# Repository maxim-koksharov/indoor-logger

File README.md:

# Air Quality Monitor — ESP8266 RTOS SDK

ESP8266-based indoor air quality monitoring system with OLED display, ENS160+AHT21 sensors, WiFi data sync, and a web dashboard.

## System Overview

Two ESP8266 devices communicating over WiFi (both connect to your home router):

```
┌────────────────────┐      WiFi (STA)       ┌────────────────────┐
│   Server (16MB)    │◄─────────────────────►│   Client (4MB)     │
│                    │    Your Home Router   │                    │
│  STA mode          │      192.168.x.x      │  STA mode          │
│  HTTP REST API     │                       │  OLED Display      │
│  Web Dashboard     │                       │  ENS160 + AHT21    │
│  Data Aggregation  │                       │  Local SPIFFS      │
│  UDP discovery     │                       │  WiFi sync         │
│  Backup WiFi       │                       │  UDP discovery     │
│  Timezone config   │                       │  Fallback SERVER_IP│
└────────────────────┘                       └────────────────────┘
```

**WiFi Mode:**
- **Server**: STA-only (connects to your router). Supports primary + backup SSID.
- **Client**: STA-only (connects to the same router). Discovers server via UDP broadcast.

**Server Discovery:** Client sends UDP broadcast to port 5000. Server responds with its IP. No static IP needed.

## Hardware Requirements

- 2× Wemos D1 Mini (ESP8266EX) — 4MB flash for the client, 16MB for the server
- 1× ENS160 + AHT21 air quality sensor module (I2C)
- 1× 0.91" SSD1306 OLED display 128×32 (I2C)
- 1× Tactile button (optional, GPIO12)
- Breadboard and jumper wires

### Wiring

All three I2C devices share a single bus (bus 0):

| Wemos Pin | GPIO | Connection |
|---|---|---|
| D1 | GPIO5 | I2C SCL (OLED + ENS160 + AHT21) |
| D2 | GPIO4 | I2C SDA (OLED + ENS160 + AHT21) |
| D5 | GPIO14 | Output LOW (button GND) |
| D6 | GPIO12 | Input pull-up (button sense) |
| 3V3 | — | VCC (all modules) |
| GND | — | GND (all modules) |

| Device | I2C Address |
|---|---|
| SSD1306 OLED | `0x3C` |
| ENS160 | `0x53` |
| AHT21 | `0x38` |

## Build System

The project uses the standard ESP-IDF CMake build system.
**SDK**: ESP8266 RTOS SDK v3.4 (`/esp/ESP8266_RTOS_SDK`)
**Toolchain**: `/esp/bin/xtensa-lx106-elf/bin`

All commands run inside the Docker container (see `AGENTS.md` for build/run instructions).

### Menuconfig (one-time setup)

```bash
# Client: Client ID, WiFi SSID/pass
idf.py -C apps/client menuconfig

# Server: WiFi SSID/pass (primary + backup)
idf.py -C apps/server menuconfig
```

### Build

```bash
idf.py -C apps/client build
idf.py -C apps/server build
```

### Flash

```bash
idf.py -C apps/client -p /dev/ttyUSB0 flash
idf.py -C apps/server -p /dev/ttyUSB1 flash
```

### Clean

```bash
idf.py -C apps/client fullclean
idf.py -C apps/server fullclean
```

> For the full command list, including monitor and erase, see `AGENTS.md`.

## WiFi Configuration

WiFi SSID and password are read from `/workspace/wifi.env` at build time. Create the file (it is gitignored):

```bash
cat > /workspace/wifi.env <<EOF
WIFI_SSID=MyHomeWiFi
WIFI_PASS=MyPassword
SERVER_IP=192.168.1.100
EOF
```

`SERVER_IP` is optional. It is used by the client as a fallback when UDP broadcast discovery is blocked by the router.

You can still override credentials via `menuconfig` or NVS if needed.

### Server

```bash
idf.py -C apps/server menuconfig
# Server Configuration → Primary WiFi SSID & Password
#                      → Backup WiFi SSID & Password (optional)
idf.py -C apps/server build
idf.py -C apps/server -p /dev/ttyUSB1 flash
```

**Operating mode:**
- The server connects to your router (STA mode)
- Supports a primary and a backup WiFi network (switches after 3 failed attempts)
- Runs a UDP discovery service on port 5000
- The client finds the server automatically via UDP broadcast
- When the network is unreachable → retries connection every 60 sec
- On wrong password → retries every 60 min

**NVS (alternative to menuconfig):**
Credentials can be stored in NVS (survives reflash):
```c
// Via provisioning or a debug script:
nvs_set_str("wifi", "sta_ssid", "YourNetwork");
nvs_set_str("wifi", "sta_pass", "YourPassword");
nvs_commit();
```
NVS takes precedence over menuconfig.

### Client

```bash
idf.py -C apps/client menuconfig
# Client Configuration → Client device identifier
#                      → WiFi SSID (same as server)
#                      → WiFi password (same as server)
idf.py -C apps/client build
idf.py -C apps/client -p /dev/ttyUSB0 flash
```

**Operating mode:**
- The client connects to the same router (STA mode)
- Sends a UDP broadcast on port 5000 to discover the server
- Automatically uses the IP returned by the server for data uploads
- Falls back to `SERVER_IP` from `wifi.env` if broadcast discovery is blocked
- Runs a state machine:
  - `DISCOVERING` — connect to WiFi, discover server
  - `CONNECTED` — upload records, apply server config, sleep for sync interval
  - `AUTONOMOUS` — keep reading sensors locally, retry discovery every hour

### What is `menuconfig` and why do I need it?

`idf.py menuconfig` opens a text-based project configuration UI.
It lets you change build parameters without editing source files:

**WiFi credentials** are read from `wifi.env` at build time. Use `menuconfig` only if you want to override them or store them in the firmware image directly.

**For the client** (`Client Configuration`):
- `Client device identifier` — unique device ID (default `test_client`).
  Used as `?id=<client_id>` when uploading to the server.
- `Display timeout` — auto-off timeout in seconds (0 = always on).
- `Discovery timeout / retry interval / default sync interval` — discovery and sync behavior.

Changes are saved in `sdkconfig` and applied on `idf.py build`.
The config options are exposed in code as `CONFIG_CLIENT_ID`, etc.

**Display:** Off by default. Turns on for 6 seconds on a button press
(2 screens × 3 seconds: temp/time → CO₂/VOC/AQI).

### Serial Monitor

`idf.py monitor` does not work inside Docker (termios error).
Use this Python script instead:

```bash
python3 -c "
import serial, time
ser = serial.Serial('/dev/ttyUSB0', 74880, timeout=1)
ser.dtr = False; ser.rts = True; time.sleep(0.1); ser.rts = False; time.sleep(2)
buf = b''; deadline = time.time() + 10
while time.time() < deadline:
    data = ser.read(4096)
    if data: buf += data
    elif len(buf) > 0: break
ser.close(); print(buf.decode('utf-8', errors='replace'))
"
```

## USB Connection & Serial Debug

Both ESP8266 boards are connected to the host via USB and are passed through to the
container by `docker compose.yml`. All build, flash, and serial debug commands
work **from inside the container** — there is no need to switch to the host shell.

### Device Mapping

| Host device | Board | Used for |
|---|---|---|
| `/dev/ttyUSB0` | Client (Wemos D1 Mini + OLED + ENS160 + AHT21) | Flash, monitor, debug |
| `/dev/ttyUSB1` | Server (Wemos D1 Mini, 16MB flash) | Flash, monitor, debug |

The container is configured with:
- `devices:` passing `/dev/ttyUSB0` and `/dev/ttyUSB1` through
- `device_cgroup_rules: c 188:* rmw` to allow `esptool` / `idf.py` to manage them
- `group_add: ["20"]` (the `dialout` group on the host) so the in-container `dev` user
  can read/write serial ports without `sudo`

### Verifying the connection

Open a shell in the container and check that the devices are visible:

```bash
docker compose run --rm bash

# Inside the container:
ls -l /dev/ttyUSB*
# crw-rw---- 1 root dialout 188, 0 ... /dev/ttyUSB0
# crw-rw---- 1 root dialout 188, 1 ... /dev/ttyUSB1

lsusb
# Bus 001 Device 005: ID 1a86:7523 QinHeng Electronics CH340 serial converter
# ...

# Confirm the in-container user is in dialout:
id
# uid=1000(dev) gid=1000(dev) groups=1000(dev),20(dialout)
```

If `/dev/ttyUSB*` are missing, the host likely does not have permission or the
devices are not enumerated yet:

```bash
# On the host:
ls -l /dev/ttyUSB*              # check device presence
sudo usermod -aG dialout $USER  # add your user to dialout (one-time)
# then log out / log in
```

### Tailing serial output (one-shot, 10s)

Capture the boot log without leaving the container:

```bash
docker compose run --rm bash -c '
  python3 -c "
import serial, time
ser = serial.Serial(\"/dev/ttyUSB0\", 74880, timeout=1)
ser.dtr = False; ser.rts = True; time.sleep(0.1); ser.rts = False; time.sleep(2)
buf = b\"\"; deadline = time.time() + 10
while time.time() < deadline:
    data = ser.read(4096)
    if data: buf += data
    elif len(buf) > 0: break
ser.close(); print(buf.decode(\"utf-8\", errors=\"replace\"))
"
'
```

For the server, replace `/dev/ttyUSB0` with `/dev/ttyUSB1`.

### Continuous log tail (interactive)

For long-running debug sessions, keep the port open and follow output:

```bash
docker compose run --rm bash

# Inside the container:
stty -F /dev/ttyUSB0 74880 raw -echo
cat /dev/ttyUSB0
# press RST on the board to see fresh boot logs
# Ctrl-C to exit
```

### Flashing a board

Flash commands work the same as on the host — just run them from inside the container:

```bash
docker compose run --rm bash

# Inside the container:
cd /workspace/apps/client
idf.py -p /dev/ttyUSB0 flash

cd /workspace/apps/server
idf.py -p /dev/ttyUSB1 flash
```

### Troubleshooting

| Symptom | Likely cause | Fix |
|---|---|---|
| `Could not open /dev/ttyUSB0` | Device busy or not present | Unplug/replug the USB cable; check `lsusb` on the host |
| `Permission denied` on `/dev/ttyUSB*` | User not in `dialout` | `sudo usermod -aG dialout $USER` on the host, then re-login |
| `esptool: failed to connect` | Wrong port or board not in flash mode | Hold `FLASH` button on Wemos D1 Mini during reset, or check wiring |
| Container cannot see `/dev/ttyUSB*` | Device path differs (e.g. `/dev/ttyACM0`) | Edit `compose.yml` `devices:` list and `device_cgroup_rules` (use `c 166:* rmw` for ACM) |
| Garbled serial output | Wrong baud rate | Wemos D1 Mini bootloader prints at **74880 baud**, runtime at **115200** |

## Self-Test

On startup, both applications log a self-test summary.
This is the primary way to verify that everything works:

**Client:**
```
=== SELF-TEST ===
  NVS: OK
  I2C: init OK (SDA=GPIO4 SCL=GPIO5)
  Display: initialized
  ENS160: detected
  AHT21: detected
  SPIFFS: OK (total=... used=...)
  Storage: 125 records saved
  Client ID: living_room
  Heap at init: 64 KB
=== END SELF-TEST ===
```

**Server:**
```
=== SELF-TEST ===
  SPIFFS: OK (total=... used=...)
  NVS: OK
  Registry: 0 clients loaded, 16 slots free
  HTTP: OK
  SNTP: synced
  STA: connected
  STA config: YourNetwork
  Time source: NTP
  Timezone: WET0WEST,M3.5.0/1,M10.5.0/2
  IP: 192.168.1.100
  Heap: 102 KB free
=== END SELF-TEST ===
```

## API Endpoints (Server)

Once connected to the router, the server is reachable on the DHCP-assigned IP (or a static one).
Use the IP directly: `http://192.168.1.100/`

| Method | URI | Description |
|---|---|---|
| GET | `/` | Web dashboard (embedded HTML) |
| GET | `/api/health` | Server status, uptime, free heap |
| GET | `/api/clients` | List all registered clients |
| GET | `/api/client?id=<id>` | Client details + last 24 records |
| POST | `/api/upload?id=<id>` | Upload sensor data JSON. Response includes `timestamp`, `sync_interval`, `name`, `timezone` |
| GET | `/api/data?id=<id>&offset=&limit=` | Query stored records |
| GET | `/api/sync-interval` | Get current sync interval (seconds) |
| POST | `/api/sync-interval?value=<sec>` | Set sync interval (seconds) |
| GET | `/api/timezone` | Get current POSIX timezone string |
| POST | `/api/timezone?value=<tz>` | Set POSIX timezone string |
| GET | `/api/client/name?id=<id>&name=<name>` | Rename a client |

### Upload JSON Format

```json
{
  "readings": [
    {"ts": 1700000000, "up": 1234, "t": 25.5, "h": 55, "c": 400, "v": 100, "a": 1}
  ]
}
```

### Data Storage Format (SPIFFS)

Each client's data is stored in `/spiffs/<client_id>.dat` as a binary ring buffer:

- **Header** (36 bytes): magic, version, client_id, max_records, write_idx, count
- **Records** (14 bytes each): timestamp, temp*100, hum*100, eco2, tvoc, aqi

## Configuration Details

### Client ID

Configured via `menuconfig` → `Client Configuration → Client device identifier`.
Used in `POST /api/upload?id=<client_id>` and as the data filename on the server.

### Server STA Mode

The server connects to your home WiFi (router) to host the HTTP API.
Credentials are set via `menuconfig` (Server Configuration → SERVER_STA_SSID/PASS,
SERVER_BACKUP_SSID/PASS) or stored in NVS (`wifi:sta_ssid`, `wifi:sta_pass`).

**Retry behavior:**
- On network not found → retry every 60 sec
- On auth failure (wrong password) → retry every 60 min
- On other connection errors → retry every 60 sec
- After 3 consecutive `NO_AP_FOUND` events → switch to backup SSID (if configured)

### Timezone

The server uses **Lisbon (WET/WEST)** by default:

```
WET0WEST,M3.5.0/1,M10.5.0/2
```

Change it at runtime from the web dashboard or via the API:

```bash
# Set to UTC
curl -X POST "http://192.168.1.100/api/timezone?value=UTC0"

# Set to Berlin
curl -X POST "http://192.168.1.100/api/timezone?value=CET-1CEST,M3.5.0/2,M10.5.0/3"
```

Common POSIX timezone strings:

| Location | POSIX TZ string |
|---|---|
| Lisbon (default) | `WET0WEST,M3.5.0/1,M10.5.0/2` |
| UTC | `UTC0` |
| London | `GMT0BST,M3.5.0/1,M10.5.0/2` |
| Berlin / Paris / Madrid / Rome | `CET-1CEST,M3.5.0/2,M10.5.0/3` |
| New York / Miami / Atlanta | `EST5EDT,M3.2.0/2,M11.1.0/2` |
| Chicago / Houston | `CST6CDT,M3.2.0/2,M11.1.0/2` |
| Denver / Salt Lake City | `MST7MDT,M3.2.0/2,M11.1.0/2` |
| Los Angeles / Seattle | `PST8PDT,M3.2.0/2,M11.1.0/2` |
| Moscow | `MSK-3` |
| Tokyo / Osaka | `JST-9` |
| Beijing / Shanghai / Hong Kong | `CST-8` |
| Singapore | `SGT-8` |
| Seoul | `KST-9` |
| Bangkok / Jakarta | `ICT-7` |
| Dubai / Abu Dhabi | `GST-4` |
| India (Mumbai / Delhi) | `IST-5:30` |
| Sydney (with DST) | `AEDT-10AEST,M10.1.0/2,M4.1.0/3` |
| Auckland (with DST) | `NZDT-12NZST,M9.5.0/2,M4.1.0/3` |
| São Paulo | `BRT3` |
| Buenos Aires | `ART3` |
| Cairo | `EET-2EEST,M4.last.4/24,M10.last.4/24` |
| Jerusalem | `IST-2IDT,M3.4.4/26,M10.5.0` |
| South Africa (Johannesburg) | `SAST-2` |
| Turkey (Istanbul) | `TRT-3` |

The timezone is stored in NVS and pushed to the client on every upload, so both devices display the same local time.

### ENS160

ENS160 requires ~3 minutes of warm-up for the first reading and ~1 hour to stabilize.
To disable ENS160 at compile time:

```c
#define ENS160_ENABLE 0
#include "ens160.h"
```

## Known ESP8266 Limitations

- **`%f` in printf/snprintf**: Not supported without `CONFIG_NEWLIB_STDOUT_FLOATING_POINT` (+28 KB). Use integer arithmetic: `(int)(val * 10) % 10`.
- **`vTaskDelay()` in `app_main()`**: Causes `rst cause: 2`. Use `xTaskCreate()` for main loops.
- **`esp_event_loop_create_default()`**: Only call once. Crashes on second call.
- **`esp_task_wdt_add()`**: Not available in v3.4. Use `esp_task_wdt_reset()` in each loop.
- **`httpd_resp_send_err()`**: Not available in v3.4. Use `httpd_resp_send_404()`/`httpd_resp_send_500()` or manually set type+send.
- **HTTP server URI wildcards**: ESP-IDF v3.4 does exact `strncmp` matching only. No `*` wildcard support. Use exact paths with query parameters.
- **mDNS not available on ESP8266**: mdns.h references `ip6_addr_t` which is not defined. Use UDP broadcast discovery (port 5000) instead.
- **WiFi retry behavior**:
  - Network not found (reason 201) → retry after 60 seconds
  - Wrong password (reason 2, 4, 204) → retry after 3600 seconds (1 hour)
  - Other disconnect reasons → retry after 60 seconds
  - After 3 consecutive NO_AP_FOUND → automatically switch to backup SSID

## Components

| Component | Description |
|---|---|
| `components/display/` | C wrapper for SSD1306 OLED driver (128×32, I2C) |
| `components/sensors/` | ENS160 (eCO₂, TVOC, AQI) + AHT21 (T, RH) I2C drivers |
| `components/fonts/` | Bitmap font library (GLCD 5x7, Terminus, Roboto, Bitocra) |
| `components/wifi/` | WiFi manager for STA-only with retry logic |

## Data Flow

```
Client                             Server
──────                             ──────
ENS160 + AHT21 → sensor_read()
        │
        ▼
data_storage_append()  ← SPIFFS ring buffer
        │
        ▼ (every sync interval, default 600s, via router)
UDP broadcast → port 5000 → discovery
        │
        ▼
wifi_sync_upload()  ─── POST /api/upload?id=<id> ──→  data_store_append()
                                                          │
                                                          ▼
                                                     SPIFFS per-client .dat
                                                          │
                                                     Web UI (GET /)
```

**Discovery Protocol:**
1. Client sends `AIRMON_DISCOVER` to UDP broadcast:5000
2. Server responds with `AIRMON_RESPONSE <ip>`
3. Client caches the IP and uses it for all upload requests
4. If broadcast is blocked, client falls back to `SERVER_IP` from `wifi.env`
5. On upload error → rediscovery on the next sync cycle

**Server Config Push:**
Each upload response includes the current `timestamp`, `sync_interval`, `name`, and `timezone`. The client applies these immediately:
- System time is set from the server timestamp
- Sync interval is updated (default 600 s, configurable via web UI/API)
- Assigned name is shown briefly on the OLED and used in the web UI
- Timezone is applied so the OLED clock matches the server

## Project Structure

```
├── cmake/                    # CMake helpers
│   └── wifi_config.cmake     # Loads wifi.env at build time
├── components/               # Shared IDF-style components
│   ├── display/              # SSD1306 OLED driver + C wrapper
│   ├── sensors/              # ENS160 + AHT21 I2C drivers
│   ├── fonts/                # Bitmap font library
│   └── wifi/                 # WiFi manager (STA-only with retry logic)
├── apps/
│   ├── server/               # Server firmware (16MB flash)
│   │   └── main/             # main.c, data_store.c, client_registry.c, http_server.c
│   └── client/               # Client firmware (4MB flash)
│       ├── main/             # main.c, data_storage.c, wifi_sync.c, button.c
│       └── partitions_client.csv
├── wifi.env                  # WiFi credentials (gitignored)
├── README.md
├── AGENTS.md
└── TODO.md
```

## License

Project code: MIT. Third-party components have their own licenses.

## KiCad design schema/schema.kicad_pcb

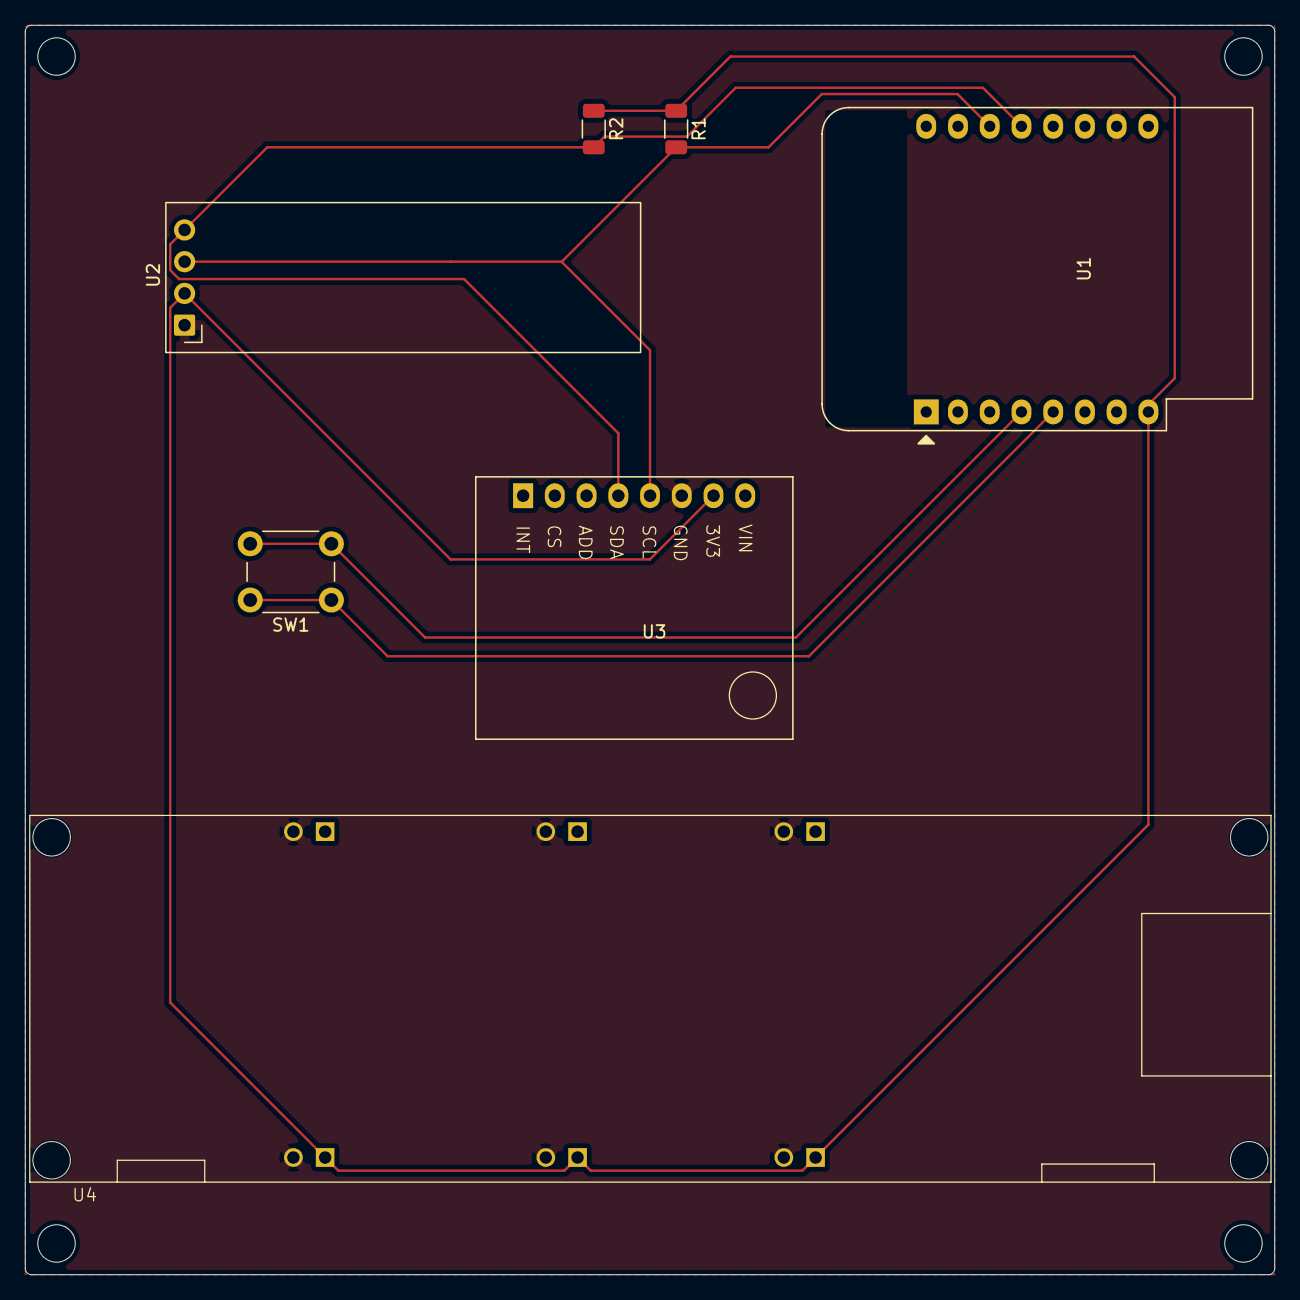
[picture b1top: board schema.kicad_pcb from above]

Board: 2 copper layers, 100.0 x 100.0 mm, 7 parts (0 on the bottom side), 6 nets.

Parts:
R1, R2: 5.1K; R_1206_3216Metric
SW1: SW_Push; SW_PUSH_6mm_H5mm
U1: WEMOS_D1_mini; WEMOS_D1_mini_light
U2: ER_OLEDM0.91_1x-I2C
U3: ENS160+AHT21
U4: 18650 Battery Shield v3

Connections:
+3.3V: R1.1, R2.1, U1.8 (3V3), U2.2 (VCC), U3.7 (3V3), U4.1 (3V)
/SCL: R1.2, U1.14 (SCL/D1), U2.3 (SCL), U3.5 (SCL/SCLK)
/SDA: R2.2, U1.13 (SDA/D2), U2.4 (SDA), U3.4 (SDA/MOSI)
/button_in: SW1.1, U1.5 (MISO/D6)
/button_out: SW1.2, U1.4 (SCK/D5)
GND: U1.10 (GND), U2.1 (GND), U3.6 (GND), U4.2 (GND)

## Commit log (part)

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2025-12-08 Init project with a draft
2025-12-08 Add necessary libraries for oled display
2025-12-08 Drafr (2)
2026-05-23 Add AGENTS.md
2026-05-23 Add Dockerfile and run script
2026-05-23 Add opencode.json
2026-05-23 Add run_docker.sh
2026-05-23 Update AGENTS.md with detailed project overview, development environment, and hardware specifications
2026-05-23 Update opencode releated files
2026-05-23 Update dockerfile
2026-05-23 Draft app
2026-05-24 Working i2c display
2026-05-24 Update AGENTS.md with data about i2c
2026-05-24 Test data on display
2026-05-24 New project structure
2026-05-24 Final of movement
2026-05-24 Changes for build test
2026-05-24 Add todo file
2026-05-24 Update structure (2)
2026-05-25 Update gitignore
2026-05-25 todo update
2026-05-25 gitignore update
2026-05-25 Update docker files
2026-05-25 Update AGENTS.md and compose.yml for improved USB device management
2026-05-25 feat: Implement client registry and data storage for HTTP server
    - Added client_registry.c and client_registry.h for managing client information.
    - Introduced data_store.c and data_store.h for handling data records associated with clients.
    - Enhanced CMakeLists.txt to include new source files and required components.
    - Developed http_server.c and http_server.h to manage HTTP requests and responses.
    - Created web_ui.h for serving a simple web interface to display client data.
    - Updated main.c to initialize the HTTP server and manage client data.
2026-05-25 docs: Update AGENTS.md and TODO.md for improved project structure and API details feat: Add partitions_client.csv for client application partition configuration
2026-05-25 feat: Implement data storage and synchronization features
    - Added data_storage.c and data_storage.h for managing client data records.
    - Updated main.c to integrate data storage functionality, including appending records and reading unsynced data.
    - Introduced wifi_sync.c and wifi_sync.h for handling WiFi synchronization of unsynced records.
    - Modified CMakeLists.txt to include new source files and required components.
    - Enhanced http_server.c to support new API endpoints for client data upload and retrieval.
    - Updated web_ui.h to reflect changes in API endpoints for fetching client details.
2026-05-25 Add README files
2026-05-25 Update AGENTS.md and TODO.md with additional notes and improvements
2026-05-25 feat: Add client configuration options and update data storage initialization
2026-05-25 feat: Enhance client registry and data store with improved timestamp handling and error management
2026-05-25 feat: Improve AHT21 initialization and reading with retry logic and enhanced logging
2026-05-25 Update README files
2026-05-26 feat: Add WiFi configuration options and UDP discovery feature
    - Introduced Kconfig options for primary and backup WiFi SSID and password.
    - Enhanced HTTP server to handle health checks and client data retrieval.
    - Implemented UDP discovery task to broadcast server IP address.
    - Updated web UI to display connection status and error messages.
    - Improved memory management by dynamically allocating client info and data records.
    - Added backup WiFi functionality to switch networks upon connection failure.
2026-05-26 feat: Add data retrieval by timestamp and enhance web UI for data visualization
2026-05-26 feat: Update data limit in data retrieval handler to enhance performance
2026-05-26 feat: Enhance display functionality and update sensor read intervals for improved performance
2026-05-26 feat: Implement SNTP initialization for time synchronization and update display with current time
2026-05-27 feat: Add aggregated data retrieval and client name editing functionality in web UI
2026-05-28 feat: Enhance button functionality with ISR handling and wakeup support; update display initialization with I2C probing
2026-05-28 Remove TODO.md
